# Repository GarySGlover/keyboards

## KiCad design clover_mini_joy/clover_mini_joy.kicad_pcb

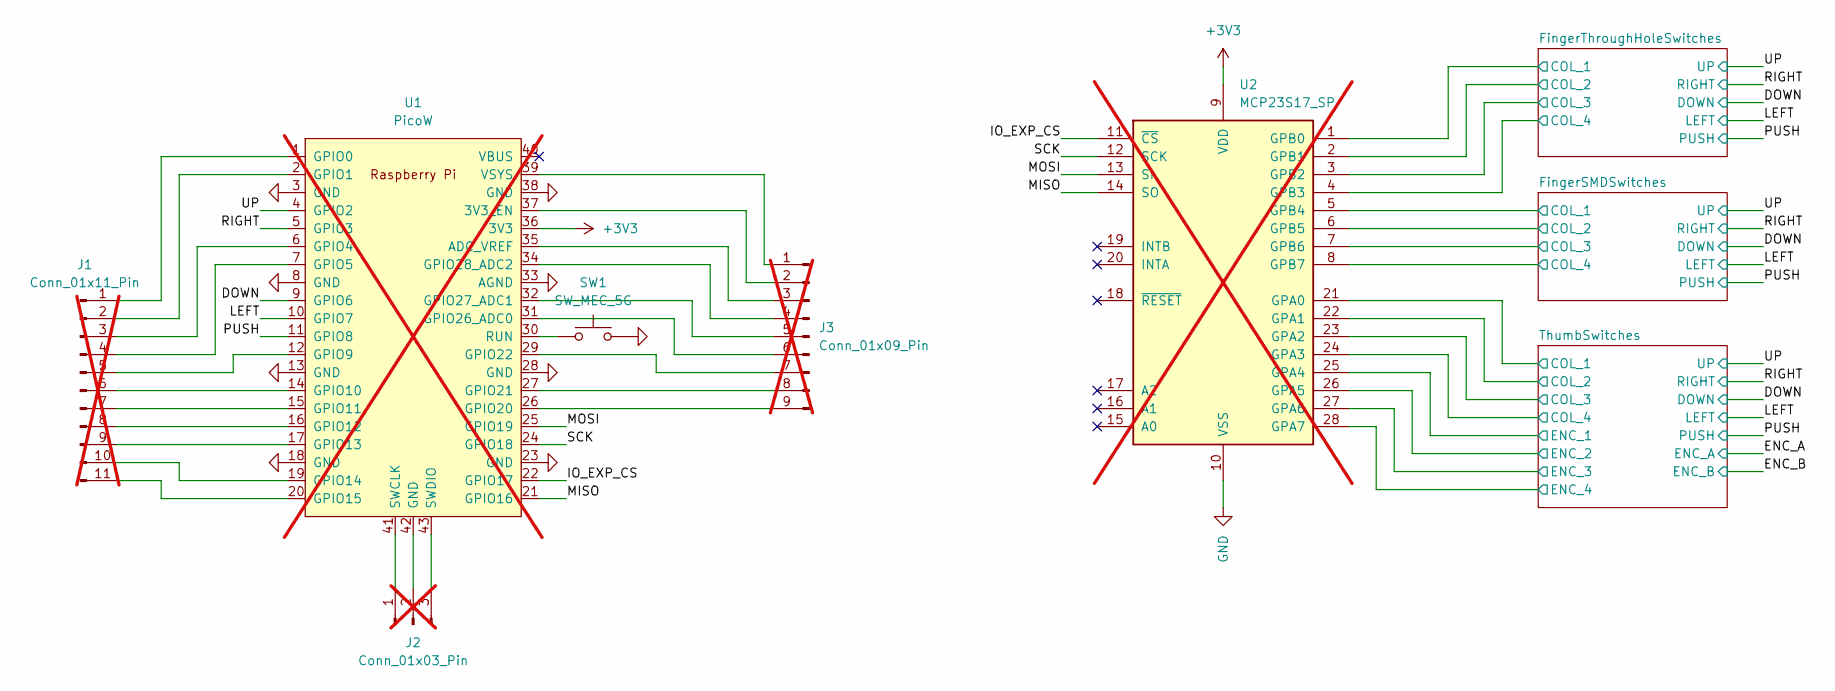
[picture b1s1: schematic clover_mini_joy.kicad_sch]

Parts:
J1: Conn_01x11_Pin; PinHeader_1x11_P1.27mm_Vertical; not fitted
J2: Conn_01x03_Pin; PinHeader_1x03_P1.27mm_Vertical; not fitted
J3: Conn_01x09_Pin; PinHeader_1x09_P1.27mm_Vertical; not fitted
SW1: SW_MEC_5G; SW_MEC_5GSH9
U1: PicoW; RPi_PicoW_SMD_TH; not fitted
U2: MCP23S17_SP; DIP-28_W7.62mm; not fitted

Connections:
+3V3: U1.36 (3V3), U2.9 (VDD)
/DOWN: U1.9 (GPIO6); also elsewhere on the board
/FingerSMDSwitches/COL_1: U2.5 (GPB4); also elsewhere on the board
/FingerSMDSwitches/COL_2: U2.6 (GPB5); also elsewhere on the board
/FingerSMDSwitches/COL_3: U2.7 (GPB6); also elsewhere on the board
/FingerSMDSwitches/COL_4: U2.8 (GPB7); also elsewhere on the board
/FingerThroughHoleSwitches/COL_1: U2.1 (GPB0); also elsewhere on the board
/FingerThroughHoleSwitches/COL_2: U2.2 (GPB1); also elsewhere on the board
/FingerThroughHoleSwitches/COL_3: U2.3 (GPB2); also elsewhere on the board
/FingerThroughHoleSwitches/COL_4: U2.4 (GPB3); also elsewhere on the board
/IO_EXP_CS: U1.22 (GPIO17), U2.11 (~CS)
/LEFT: U1.10 (GPIO7); also elsewhere on the board
/MISO: U1.21 (GPIO16), U2.14 (SO)
/MOSI: U1.25 (GPIO19), U2.13 (SI)
/PUSH: U1.11 (GPIO8); also elsewhere on the board
/RIGHT: U1.5 (GPIO3); also elsewhere on the board
/SCK: U1.24 (GPIO18), U2.12 (SCK)
/ThumbSwitches/COL_1: U2.21 (GPA0); also elsewhere on the board
/ThumbSwitches/COL_2: U2.22 (GPA1); also elsewhere on the board
/ThumbSwitches/COL_3: U2.23 (GPA2); also elsewhere on the board
/ThumbSwitches/COL_4: U2.24 (GPA3); also elsewhere on the board
/ThumbSwitches/ENC_1: U2.25 (GPA4); also elsewhere on the board
/ThumbSwitches/ENC_2: U2.26 (GPA5); also elsewhere on the board
/ThumbSwitches/ENC_3: U2.27 (GPA6); also elsewhere on the board
/ThumbSwitches/ENC_4: U2.28 (GPA7); also elsewhere on the board
/UP: U1.4 (GPIO2); also elsewhere on the board
GND: SW1.3 (B), SW1.4 (B), U1.3 (GND), U1.8 (GND), U1.13 (GND), U1.18 (GND), U1.23 (GND), U1.28 (GND), U1.33 (AGND), U1.38 (GND), U2.10 (VSS); also elsewhere on the board
unnamed: J1.1, U1.1 (GPIO0)
unnamed: J1.2, U1.2 (GPIO1)
unnamed: J1.3, U1.6 (GPIO4)
unnamed: J1.4, U1.7 (GPIO5)
unnamed: J1.5, U1.12 (GPIO9)
unnamed: J1.6, U1.14 (GPIO10)
unnamed: J1.7, U1.15 (GPIO11)
unnamed: J1.8, U1.16 (GPIO12)
unnamed: J1.9, U1.17 (GPIO13)
unnamed: J1.10, U1.19 (GPIO14)
unnamed: J1.11, U1.20 (GPIO15)
unnamed: J2.1, U1.41 (SWCLK)
unnamed: J2.2, U1.42 (GND)
unnamed: J2.3, U1.43 (SWDIO)
unnamed: J3.1, U1.39 (VSYS)
unnamed: J3.2, U1.37 (3V3_EN)
unnamed: J3.3, U1.35 (ADC_VREF)
unnamed: J3.4, U1.34 (GPIO28_ADC2)
unnamed: J3.5, U1.32 (GPIO27_ADC1)
unnamed: J3.6, U1.31 (GPIO26_ADC0)
unnamed: J3.7, U1.29 (GPIO22)
unnamed: J3.8, U1.27 (GPIO21)
unnamed: J3.9, U1.26 (GPIO20)
unnamed: SW1.1 (A), SW1.2 (A), U1.30 (RUN)

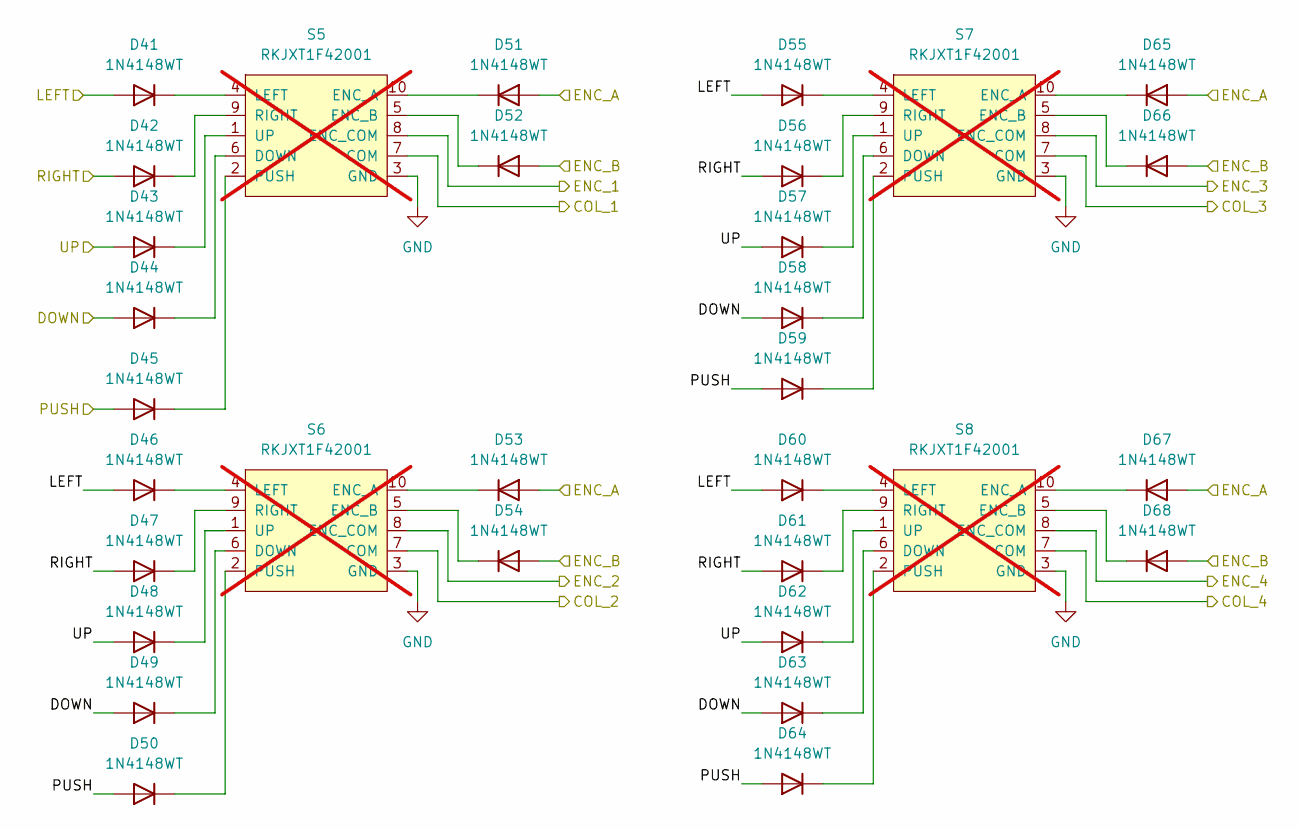
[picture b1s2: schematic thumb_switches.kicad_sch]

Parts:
D41, D42, D43, D44, D45, D46, D47, D48, D49, D50, D51, D52, D53, D54, D55, D56, D57, D58, D59, D60, D61, D62, D63, D64, D65, D66, D67, D68: 1N4148WT; D_SOD-523
S5, S6, S7, S8: RKJXT1F42001; not fitted

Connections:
/DOWN: D44.2 (A), D49.2 (A), D58.2 (A), D63.2 (A); also elsewhere on the board
/ENC_A: D51.2 (A), D53.2 (A), D65.2 (A), D67.2 (A)
/ENC_B: D52.2 (A), D54.2 (A), D66.2 (A), D68.2 (A)
/LEFT: D41.2 (A), D46.2 (A), D55.2 (A), D60.2 (A); also elsewhere on the board
/PUSH: D45.2 (A), D50.2 (A), D59.2 (A), D64.2 (A); also elsewhere on the board
/RIGHT: D42.2 (A), D47.2 (A), D56.2 (A), D61.2 (A); also elsewhere on the board
/ThumbSwitches/COL_1: S5.7 (COM); also elsewhere on the board
/ThumbSwitches/COL_2: S6.7 (COM); also elsewhere on the board
/ThumbSwitches/COL_3: S7.7 (COM); also elsewhere on the board
/ThumbSwitches/COL_4: S8.7 (COM); also elsewhere on the board
/ThumbSwitches/ENC_1: S5.8 (ENC_COM); also elsewhere on the board
/ThumbSwitches/ENC_2: S6.8 (ENC_COM); also elsewhere on the board
/ThumbSwitches/ENC_3: S7.8 (ENC_COM); also elsewhere on the board
/ThumbSwitches/ENC_4: S8.8 (ENC_COM); also elsewhere on the board
/UP: D43.2 (A), D48.2 (A), D57.2 (A), D62.2 (A); also elsewhere on the board
GND: S5.3 (GND), S6.3 (GND), S7.3 (GND), S8.3 (GND); also elsewhere on the board
unnamed: D41.1 (K), S5.4 (LEFT)
unnamed: D42.1 (K), S5.9 (RIGHT)
unnamed: D43.1 (K), S5.1 (UP)
unnamed: D44.1 (K), S5.6 (DOWN)
unnamed: D45.1 (K), S5.2 (PUSH)
unnamed: D46.1 (K), S6.4 (LEFT)
unnamed: D47.1 (K), S6.9 (RIGHT)
unnamed: D48.1 (K), S6.1 (UP)
unnamed: D49.1 (K), S6.6 (DOWN)
unnamed: D50.1 (K), S6.2 (PUSH)
unnamed: D51.1 (K), S5.10 (ENC_A)
unnamed: D52.1 (K), S5.5 (ENC_B)
unnamed: D53.1 (K), S6.10 (ENC_A)
unnamed: D54.1 (K), S6.5 (ENC_B)
unnamed: D55.1 (K), S7.4 (LEFT)
unnamed: D56.1 (K), S7.9 (RIGHT)
unnamed: D57.1 (K), S7.1 (UP)
unnamed: D58.1 (K), S7.6 (DOWN)
unnamed: D59.1 (K), S7.2 (PUSH)
unnamed: D60.1 (K), S8.4 (LEFT)
unnamed: D61.1 (K), S8.9 (RIGHT)
unnamed: D62.1 (K), S8.1 (UP)
unnamed: D63.1 (K), S8.6 (DOWN)
unnamed: D64.1 (K), S8.2 (PUSH)
unnamed: D65.1 (K), S7.10 (ENC_A)
unnamed: D66.1 (K), S7.5 (ENC_B)
unnamed: D67.1 (K), S8.10 (ENC_A)
unnamed: D68.1 (K), S8.5 (ENC_B)

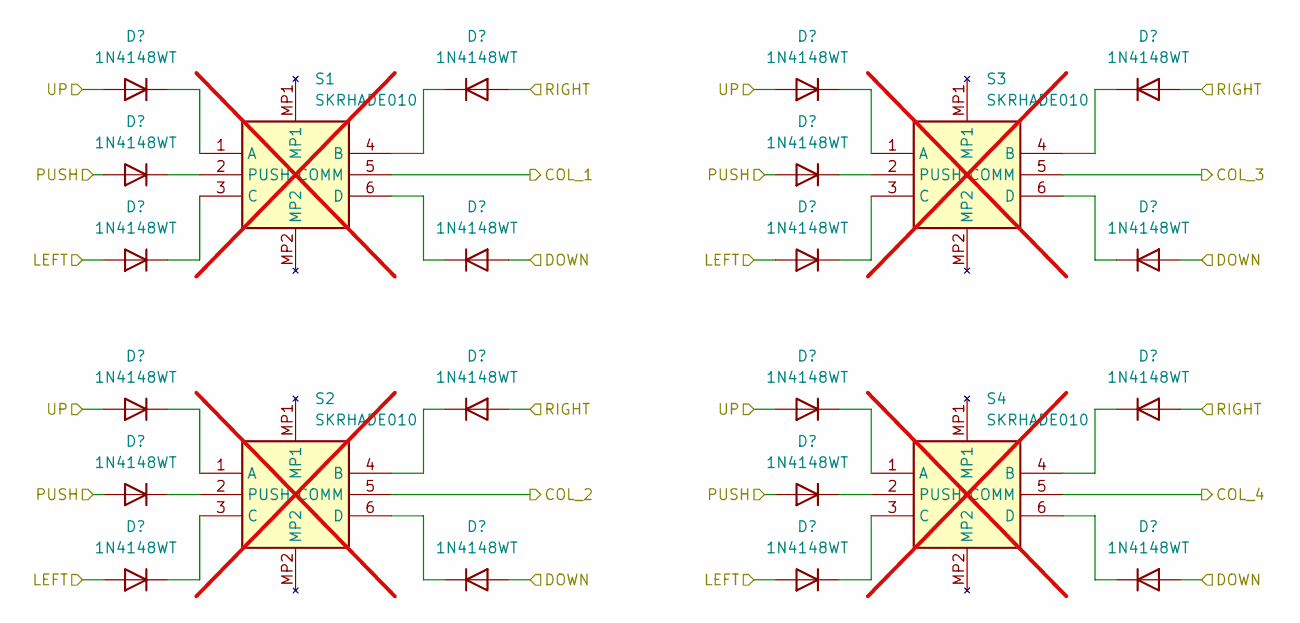
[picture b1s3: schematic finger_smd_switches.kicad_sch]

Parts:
D21, D22, D23, D24, D25, D26, D27, D28, D29, D30, D31, D32, D33, D34, D35, D36, D37, D38, D39, D40: 1N4148WT; D_SOD-523
S1, S2, S3, S4: SKRHADE010; Manufacturer_Part_Number SKRHADE010; Mouser Part Number 688-SKRHAD; not fitted

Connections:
/DOWN: D28.2 (A), D30.2 (A), D38.2 (A), D40.2 (A); also elsewhere on the board
/FingerSMDSwitches/COL_1: S1.5 (COMM); also elsewhere on the board
/FingerSMDSwitches/COL_2: S2.5 (COMM); also elsewhere on the board
/FingerSMDSwitches/COL_3: S3.5 (COMM); also elsewhere on the board
/FingerSMDSwitches/COL_4: S4.5 (COMM); also elsewhere on the board
/LEFT: D23.2 (A), D26.2 (A), D33.2 (A), D36.2 (A); also elsewhere on the board
/PUSH: D22.2 (A), D25.2 (A), D32.2 (A), D35.2 (A); also elsewhere on the board
/RIGHT: D27.2 (A), D29.2 (A), D37.2 (A), D39.2 (A); also elsewhere on the board
/UP: D21.2 (A), D24.2 (A), D31.2 (A), D34.2 (A); also elsewhere on the board
unnamed: D21.1 (K), S1.1 (A)
unnamed: D22.1 (K), S1.2 (PUSH)
unnamed: D23.1 (K), S1.3 (C)
unnamed: D24.1 (K), S2.1 (A)
unnamed: D25.1 (K), S2.2 (PUSH)
unnamed: D26.1 (K), S2.3 (C)
unnamed: D27.1 (K), S1.4 (B)
unnamed: D28.1 (K), S1.6 (D)
unnamed: D29.1 (K), S2.4 (B)
unnamed: D30.1 (K), S2.6 (D)
unnamed: D31.1 (K), S3.1 (A)
unnamed: D32.1 (K), S3.2 (PUSH)
unnamed: D33.1 (K), S3.3 (C)
unnamed: D34.1 (K), S4.1 (A)
unnamed: D35.1 (K), S4.2 (PUSH)
unnamed: D36.1 (K), S4.3 (C)
unnamed: D37.1 (K), S3.4 (B)
unnamed: D38.1 (K), S3.6 (D)
unnamed: D39.1 (K), S4.4 (B)
unnamed: D40.1 (K), S4.6 (D)

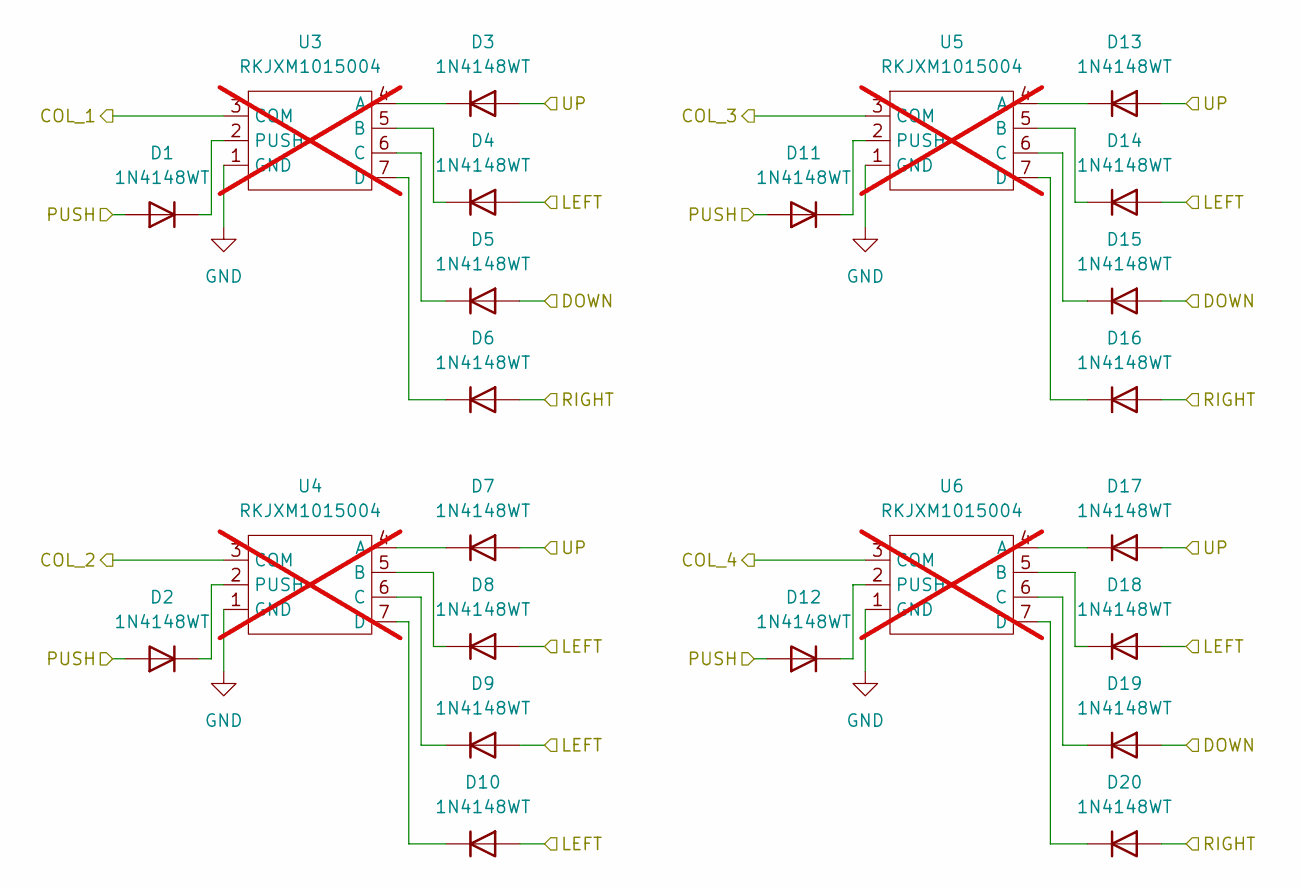
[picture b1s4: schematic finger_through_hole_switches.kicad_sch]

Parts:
D1, D2, D3, D4, D5, D6, D7, D8, D9, D10, D11, D12, D13, D14, D15, D16, D17, D18, D19, D20: 1N4148WT; D_SOD-523
U3, U4, U5, U6: RKJXM1015004; not fitted

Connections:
/DOWN: D5.2 (A), D15.2 (A), D19.2 (A); also elsewhere on the board
/FingerThroughHoleSwitches/COL_1: U3.3 (COM); also elsewhere on the board
/FingerThroughHoleSwitches/COL_2: U4.3 (COM); also elsewhere on the board
/FingerThroughHoleSwitches/COL_3: U5.3 (COM); also elsewhere on the board
/FingerThroughHoleSwitches/COL_4: U6.3 (COM); also elsewhere on the board
/LEFT: D4.2 (A), D8.2 (A), D9.2 (A), D10.2 (A), D14.2 (A), D18.2 (A); also elsewhere on the board
/PUSH: D1.2 (A), D2.2 (A), D11.2 (A), D12.2 (A); also elsewhere on the board
/RIGHT: D6.2 (A), D16.2 (A), D20.2 (A); also elsewhere on the board
/UP: D3.2 (A), D7.2 (A), D13.2 (A), D17.2 (A); also elsewhere on the board
GND: U3.1 (GND), U4.1 (GND), U5.1 (GND), U6.1 (GND); also elsewhere on the board
unnamed: D1.1 (K), U3.2 (PUSH)
unnamed: D2.1 (K), U4.2 (PUSH)
unnamed: D3.1 (K), U3.4 (A)
unnamed: D4.1 (K), U3.5 (B)
unnamed: D5.1 (K), U3.6 (C)
unnamed: D6.1 (K), U3.7 (D)
unnamed: D7.1 (K), U4.4 (A)
unnamed: D8.1 (K), U4.5 (B)
unnamed: D9.1 (K), U4.6 (C)
unnamed: D10.1 (K), U4.7 (D)
unnamed: D11.1 (K), U5.2 (PUSH)
unnamed: D12.1 (K), U6.2 (PUSH)
unnamed: D13.1 (K), U5.4 (A)
unnamed: D14.1 (K), U5.5 (B)
unnamed: D15.1 (K), U5.6 (C)
unnamed: D16.1 (K), U5.7 (D)
unnamed: D17.1 (K), U6.4 (A)
unnamed: D18.1 (K), U6.5 (B)
unnamed: D19.1 (K), U6.6 (C)
unnamed: D20.1 (K), U6.7 (D)

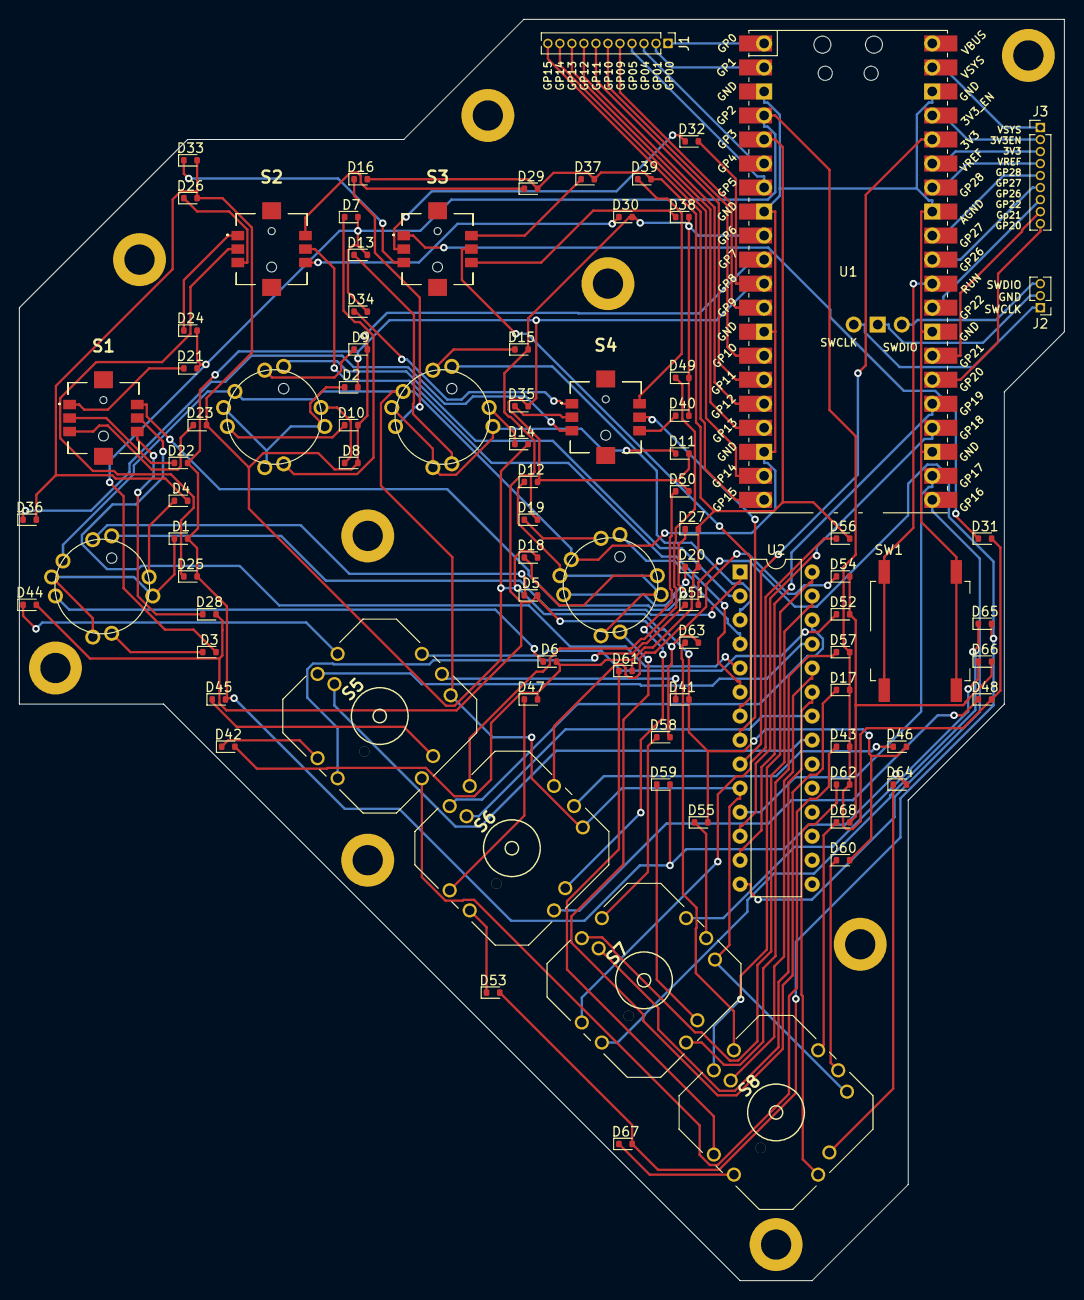
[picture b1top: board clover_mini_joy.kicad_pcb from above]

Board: 2 copper layers, 110.5 x 133.3 mm, 95 parts (0 on the bottom side), 121 nets.

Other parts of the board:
REF1, REF2, REF3, REF4, REF5, REF7, REF8, REF9, REF10: MountingHole_3.2mm_M3_DIN965_Pad

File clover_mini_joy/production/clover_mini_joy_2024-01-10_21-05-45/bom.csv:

Designator,Footprint,Quantity,Value,LCSC Part #
"D1, D10, D11, D12, D13, D14, D15, D16, D17, D18, D19, D2, D20, D21, D22, D23, D24, D25, D26, D27, D28, D29, D3, D30, D31, D32, D33, D34, D35, D36, D37, D38, D39, D4, D40, D41, D42, D43, D44, D45, D46, D47, D48, D49, D5, D50, D51, D52, D53, D54, D55, D56, D57, D58, D59, D6, D60, D61, D62, D63, D64, D65, D66, D67, D68, D7, D8, D9",D_SOD-523,68,1N4148WT,
J1,PinHeader_2x12_P1.00mm_Vertical_SMD,1,Conn_02x12_Counter_Clockwise,
"S1, S2, S3, S4",SKRHADE010,4,SKRHADE010,
"S5, S6, S7, S8",RKJXT1F42001,4,RKJXT1F42001,
SW1,SW_MEC_5GSH9,1,SW_MEC_5G,
U1,RPi_PicoW_SMD_TH,1,PicoW,
U2,DIP-28_W7.62mm,1,MCP23S17_SP,
"U3, U4, U5, U6",RKJXM1015004,4,RKJXM1015004,

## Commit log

2024-01-13 Clover digger circuit board for development
